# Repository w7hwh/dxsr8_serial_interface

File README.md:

# DX-SR8 Serial Interface

## Introduction

Since I have a DX-SR8 and a few Raspberry Pi Picos sitting around I decided to try building an interface based on a Raspberry Pi Pico 2. If nothing else the project will force me to become more familiar with MicroPython.

Back in 2013 AJ9BM did an analysis of the communication between the DX-SR8's chassis and its front panel. He found out a great deal about the protocol and built working prototypes but he eventually abandoned the project. More about his work is in [aj9bm.md](./aj9bm.md).
 
The micropython didn't work so well for me so I've switched to programming in C to run under freeRTOS. This was picked because of the same reason many things are decided, I have experience with both C and freeRTOS. :^) Initially I'm using a "Blue Pill" board with a cpu labeled STM32F103CBT6 . The ST-INFO utility says it has 256k flash and 64k of ram instead of the lower amounts that chip is supposed to have. 

---

## Planned stages are:

- [x] Micropython firmware to continue analyzing the protocol using a breadboarded RPi Pico 2. Essentially use the Pico as a double channel usb-serial adapter with some analysis/decoding capability. This includes converting the original python2 to python3.

- [ ] Firmware to actually control the radio. Currently planned to be in C running under freeRTOS.

- [ ] Design a board.

- [ ] Add capability to send CAT commands to control the rig.

- [ ] Add capability to send/receive audio?

---

## Contents:

- aj9bm_code/ -- The original python analysis code AJ9BM wrote back in 2013.
- board/ -- Board design files
- documentation/ -- Documenting the protocol between radio and head.
- firmware_c/ -- My code to run in C on a STM32 cpu. (currently a STM32F103 based 'Blue Pill' board.)
- firmware_python/ -- My code to run in MicroPython on a Raspberry Pi Pico 2. This has been abandoned in favor of the C version.
- images/ -- Images

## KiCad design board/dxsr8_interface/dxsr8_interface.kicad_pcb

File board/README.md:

# DXSR8 Serial Interface Design Files

## GPIO Usage

- GP0  
- GP1  
- GP2  
- GP3  
- GP4	UART1-TX serial send to chassis
- GP5	UART1-RX serial receive from head
- GP6  
- GP7  
- GP8  
- GP9  
- GP10  
- GP11  
- GP12	UART0-TX serial send to head
- GP13	UART0-RX serial receive from chassis
- GP14  
- GP15  
- GP16	I2C0-SDA for SH1106 based display
- GP17	I2C0-SCL for SH1106 based display
- GP18  
- GP19  
- GP20  
- GP21  
- GP22  GP22-RELAY-CTL
- GP23  (wireless module) OP wireless power on signal
- GP24  (wireless module) OP/IP SPI data/IRQ
- GP25  (wireless module) OP SPI CS, when high also enable GP29 to read VSYS
- GP26	ADC0 monitor power from chassis
- GP27  ADC1 monitor power from USB
- GP28  
- GP29  (wireless module) OP/IP SPI CLK/ADC3 mode read VSYS/3
- WL-GPOI0  (wireless module) OP to LED
- WL-GPOI1  (wireless module) OP controls SMPS power save
- WL-GPOI2  (wireless module) IP high if VBUS present

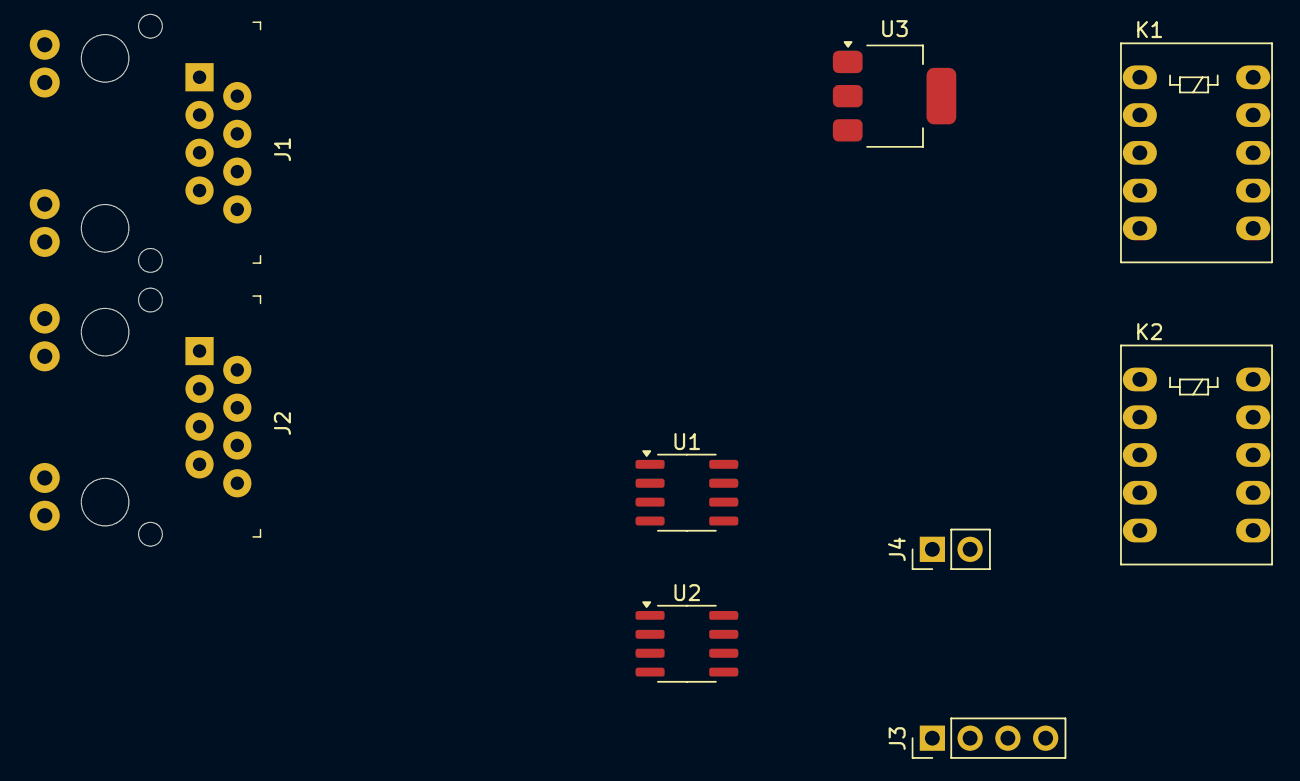
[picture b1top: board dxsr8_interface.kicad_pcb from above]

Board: 2 copper layers, 9 parts (0 on the bottom side), 9 nets, no tracks yet.

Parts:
J1, J2: RJ45; Ethernet_Jack_ARJC02-111008B
J3: PinHeader_1x04_P2.54mm_Vertical
J4: NP; PinHeader_1x02_P2.54mm_Vertical
K1, K2: Relay_DPDT; Relay_DPDT_FRT5
U1, U2: ADuM1201AR; SOIC-8_3.9x4.9mm_P1.27mm
U3: AMS1117-5.0; SOT-223-3_TabPin2

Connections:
+8V: J1.3, J2.3, U3.3 (VI)
/CLN: J1.4, J2.4
/CRXD: J1.2, J2.2
/CTXD: J1.1, J2.1
/MIC: J1.5, J2.5
/SP: J1.7, J2.7
/SPG: J1.8, J2.8
GND: J3.1, J4.1
GND1: J1.6, J1.9, J2.6, J2.9, J4.2, U3.1 (GND)

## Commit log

2025-07-08 rewrite readme and other housekeeping
2025-07-08 more housekeeping
2025-07-09 document GPIO usage
2025-07-09 work on the code
2025-07-09 more info about aj9bm work
2025-07-10 further expanded info on aj9bm's work
2025-07-12 work
2025-07-13 switch to ADM1201 isolators, add regulator for them
2025-07-15 work on board design
2025-07-16 progress, most head decoding works now
2025-07-16 add relay control to gpio list
2025-07-16 add .gitignore listing capture directory
2025-07-17 add start of protocol documentation
2025-07-18 decided wifi is not necessare, switch from pico 2w to pico 2
2025-07-18 add info to protocol documentation
2025-07-19 work, moved common routines to new utility.py
2025-07-20 add images of front panel
2025-07-23 work on bit documentation
2025-07-24 added image of display with all segments on.
2025-08-25 last update of the python version as I switch to C
2025-08-25 copied the final python version as base for new C version.
2025-08-25 update readme for switch to C and freeRTOS.
2025-08-25 fix typo in readme.
2025-09-07 add freertos c version
2025-09-07 add pinout diagram of blue pill board
2025-09-08 correct readme
